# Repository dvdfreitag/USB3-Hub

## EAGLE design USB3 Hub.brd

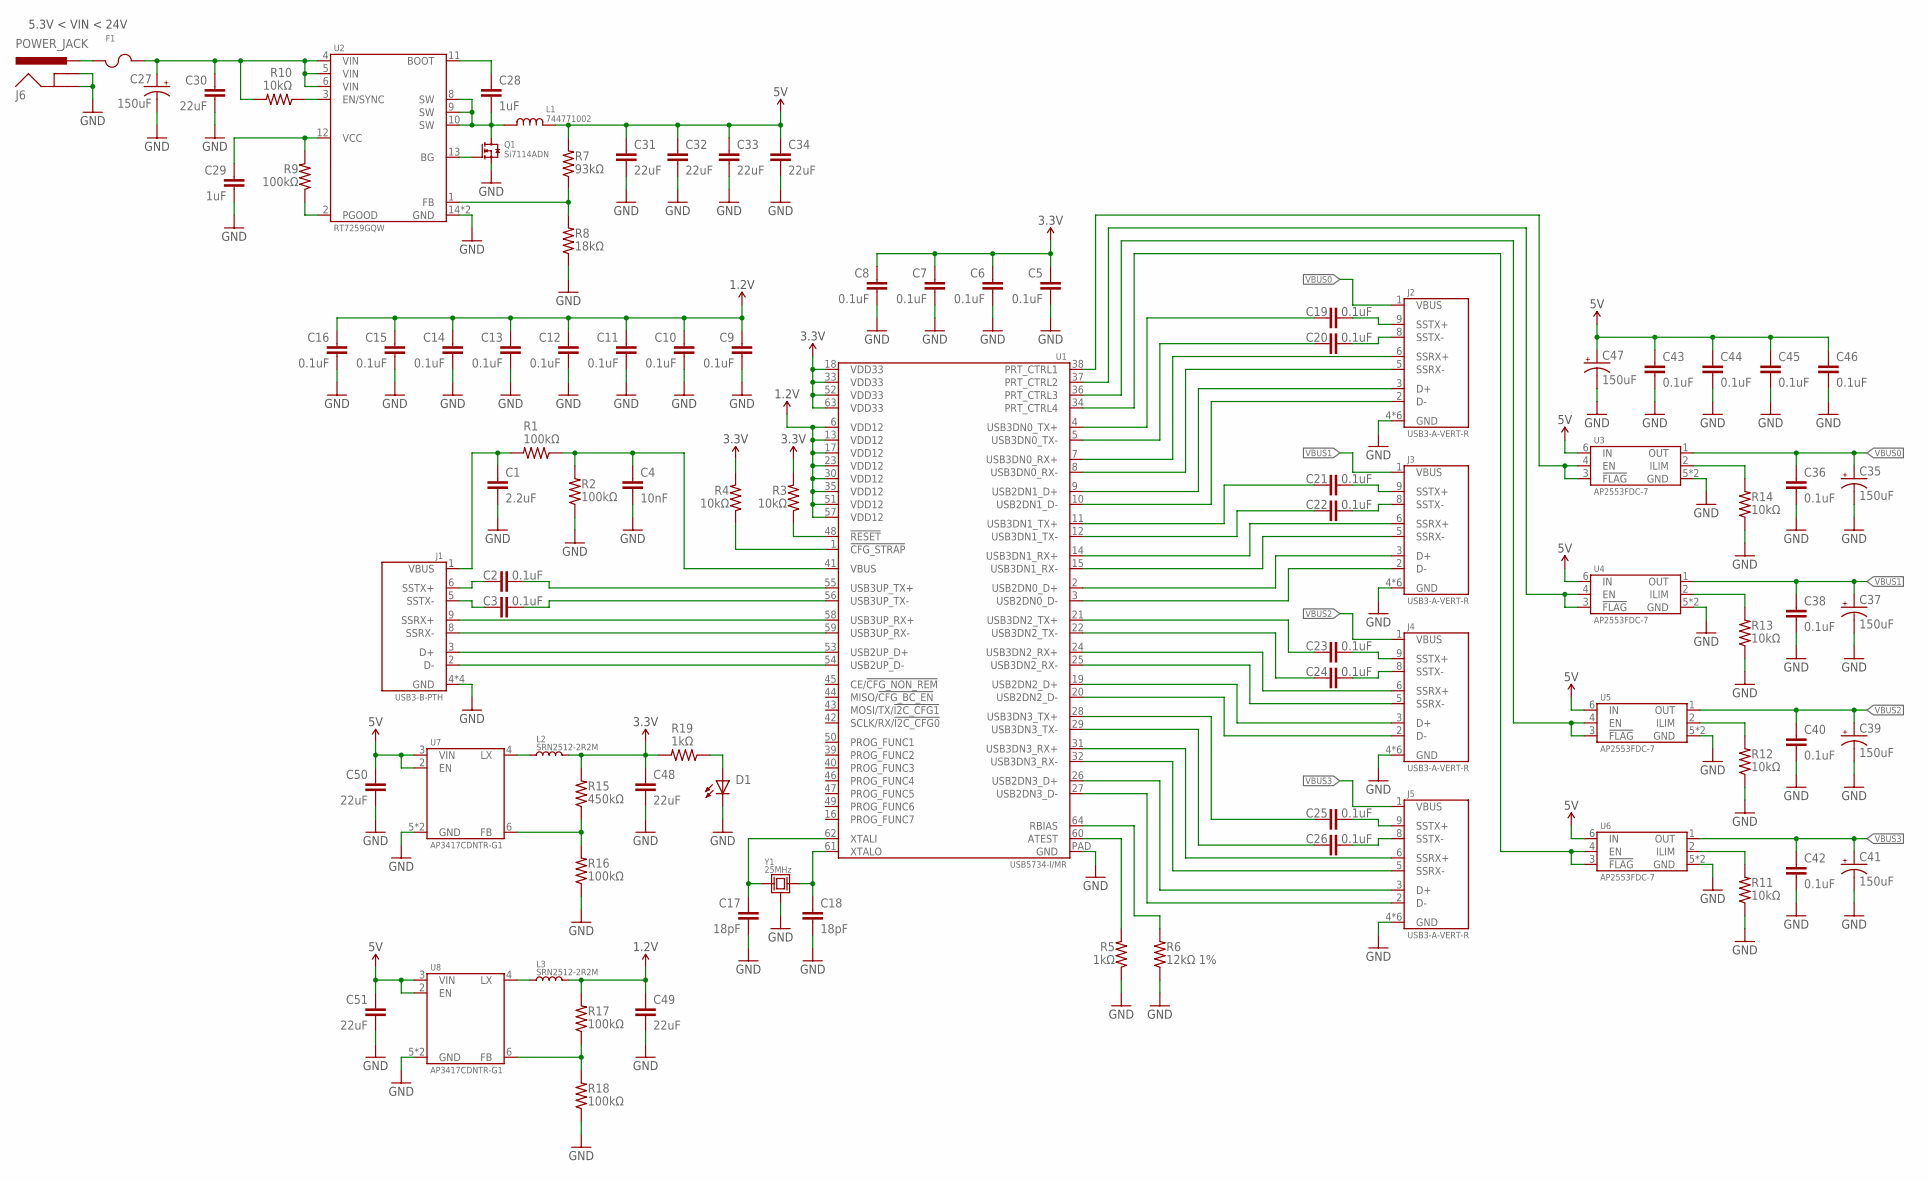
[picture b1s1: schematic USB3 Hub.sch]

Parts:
C1: 2.2uF; 0603-CAP
C2, C3, C5, C6, C7, C8, C9, C10, C11, C12, C13, C14, C15, C16, C19, C20, C21, C22, C23, C24, C25, C26, C36, C38, C40, C42, C43, C44, C45, C46: 0.1uF; 0603-CAP
C4: 10nF; 0603-CAP
C17, C18: 18pF; 0603-CAP
C27, C35, C37, C39, C41, C47: 150uF; CAP_POL-6.6X6.6
C28, C29: 1uF; 0603-CAP
C30, C31, C32, C33, C34, C48, C49, C50, C51: 22uF; 0603-CAP
D1: LED-0805; 0805-LED
F1: PTC-1812; 1812-PTC
J1: USB3-B-PTH; GSB4211311WEU
J2, J3, J4, J5: USB3-A-VERT-R; GSB4116341HR
J6: POWER_JACK; BARREL-POWER_2.1MMX5.5MM
L1: 744771002
L2, L3: SRN2512-2R2M; SRN2512
Q1: Si7114ADN; POWERPAK
R1, R2, R9, R16, R17, R18: 100kΩ; 0603-CAP
R3, R4, R10, R11, R12, R13, R14: 10kΩ; 0603-CAP
R5, R19: 1kΩ; 0603-CAP
R6: 12kΩ 1%; 0603-CAP
R7: 93kΩ; 0603-CAP
R8: 18kΩ; 0603-CAP
R15: 450kΩ; 0603-CAP
U1: USB5734-I/MR; VQFN-64-9MM
U2: RT7259GQW; WDFN-14-4X3
U3, U4, U5, U6: AP2553FDC-7; UDFN6-2020
U7, U8: AP3417CDNTR-G1; UDFN6-2020
Y1: 25MHz; FA-238

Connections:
1.2V: C9.1, C10.1, C11.1, C12.1, C13.1, C14.1, C15.1, C16.1, C49.1, L3.2, R17.2, U1.6 (VDD12), U1.13 (VDD12), U1.17 (VDD12), U1.23 (VDD12), U1.30 (VDD12), U1.35 (VDD12), U1.51 (VDD12), U1.57 (VDD12)
3.3V: C5.1, C6.1, C7.1, C8.1, C48.1, L2.2, R3.2, R4.2, R15.2, R19.2, U1.18 (VDD33), U1.33 (VDD33), U1.52 (VDD33), U1.63 (VDD33)
5V: C31.1, C32.1, C33.1, C34.1, C43.1, C44.1, C45.1, C46.1, C47.+, C50.1, C51.1, L1.P$2, R7.2, U3.6 (IN), U4.6 (IN), U5.6 (IN), U6.6 (IN), U7.2 (EN), U7.3 (VIN), U8.2 (EN), U8.3 (VIN)
D0_N: J2.2 (D-), U1.10 (USB2DN1_D-)
D0_P: J2.3 (D+), U1.9 (USB2DN1_D+)
D1_N: J3.2 (D-), U1.3 (USB2DN0_D-)
D1_P: J3.3 (D+), U1.2 (USB2DN0_D+)
D2_N: J4.2 (D-), U1.20 (USB2DN2_D-)
D2_P: J4.3 (D+), U1.19 (USB2DN2_D+)
D3_N: J5.2 (D-), U1.27 (USB2DN3_D-)
D3_P: J5.3 (D+), U1.26 (USB2DN3_D+)
D_N: J1.2 (D-), U1.54 (USB2UP_D-)
D_P: J1.3 (D+), U1.53 (USB2UP_D+)
GND: C1.2, C4.2, C5.2, C6.2, C7.2, C8.2, C9.2, C10.2, C11.2, C12.2, C13.2, C14.2, C15.2, C16.2, C17.2, C18.2, C27.-, C29.2, C30.2, C31.2, C32.2, C33.2, C34.2, C35.-, C36.2, C37.-, C38.2, C39.-, C40.2, C41.-, C42.2, C43.2, C44.2, C45.2, C46.2, C47.-, C48.2, C49.2, C50.2, C51.2, D1.C, J1.4 (GND), J1.7 (GND), J1.P$10 (GND), J1.P$11 (GND), J2.4 (GND), J2.7 (GND), J2.P$1 (GND), J2.P$2 (GND), J2.P$3 (GND), J2.P$4 (GND), J3.4 (GND), J3.7 (GND), J3.P$1 (GND), J3.P$2 (GND), J3.P$3 (GND), J3.P$4 (GND), J4.4 (GND), J4.7 (GND), J4.P$1 (GND), J4.P$2 (GND), J4.P$3 (GND), J4.P$4 (GND), J5.4 (GND), J5.7 (GND), J5.P$1 (GND), J5.P$2 (GND), J5.P$3 (GND), J5.P$4 (GND), J6.2 (GND), J6.3 (GNDBREAK), Q1.1 (SOURCE), Q1.2 (SOURCE), Q1.3 (SOURCE), R2.1, R5.1, R6.1, R8.1, R11.1, R12.1, R13.1, R14.1, R16.1, R18.1, U1.PAD (GND), U2.14 (GND), U2.PAD (GND), U3.5 (GND), U3.PAD (GND), U4.5 (GND), U4.PAD (GND), U5.5 (GND), U5.PAD (GND), U6.5 (GND), U6.PAD (GND), U7.5 (GND), U7.PAD (GND), U8.5 (GND), U8.PAD (GND), Y1.2 (GND), Y1.4 (GND)
unnamed: F1.1, J6.1 (PWR)
unnamed: C27.+, C30.1, F1.2, R10.2, U2.4 (VIN), U2.5 (VIN), U2.6 (VIN)
unnamed: R7.1, R8.2, U2.1 (FB)
unnamed: Q1.4 (GATE), U2.13 (BG)
unnamed: C1.1, J1.1 (VBUS), R1.2
unnamed: R12.2, U5.2 (ILIM)
unnamed: C28.2, L1.P$1, Q1.5 (DRAIN), Q1.6 (DRAIN), Q1.7 (DRAIN), Q1.8 (DRAIN), Q1.9 (DRAIN), Q1.10 (DRAIN), Q1.11 (DRAIN), U2.8 (SW), U2.9 (SW), U2.10 (SW)
unnamed: C28.1, U2.11 (BOOT)
unnamed: C29.1, R9.2, U2.12 (VCC)
unnamed: C4.1, R1.1, R2.2, U1.41 (VBUS)
unnamed: R9.1, U2.2 (PGOOD)
unnamed: R3.1, U1.48 (!RESET)
unnamed: R4.1, U1.1 (!CFG_STRAP)
unnamed: C17.1, U1.62 (XTALI), Y1.1
unnamed: C18.1, U1.61 (XTALO), Y1.3 (2)
unnamed: R5.2, U1.60 (ATEST)
unnamed: R6.2, U1.64 (RBIAS)
unnamed: R10.1, U2.3 (EN/SYNC)
unnamed: R11.2, U6.2 (ILIM)
unnamed: L3.1, U8.4 (LX)
unnamed: U1.36 (PRT_CTRL3), U5.3 (!FLAG), U5.4 (EN)
unnamed: U1.38 (PRT_CTRL1), U3.3 (!FLAG), U3.4 (EN)
unnamed: U1.37 (PRT_CTRL2), U4.3 (!FLAG), U4.4 (EN)
unnamed: R14.2, U3.2 (ILIM)
unnamed: R17.1, R18.2, U8.6 (FB)
unnamed: L2.1, U7.4 (LX)
unnamed: R13.2, U4.2 (ILIM)
unnamed: U1.34 (PRT_CTRL4), U6.3 (!FLAG), U6.4 (EN)
unnamed: R15.1, R16.2, U7.6 (FB)
unnamed: D1.A, R19.1
R0_N: J2.5 (SSRX-), U1.8 (USB3DN0_RX-)
R0_P: J2.6 (SSRX+), U1.7 (USB3DN0_RX+)
R1_N: J3.5 (SSRX-), U1.15 (USB3DN1_RX-)
R1_P: J3.6 (SSRX+), U1.14 (USB3DN1_RX+)
R2_N: J4.5 (SSRX-), U1.25 (USB3DN2_RX-)
R2_P: J4.6 (SSRX+), U1.24 (USB3DN2_RX+)
R3_N: J5.5 (SSRX-), U1.32 (USB3DN3_RX-)
R3_P: J5.6 (SSRX+), U1.31 (USB3DN3_RX+)
R_N: J1.8 (SSRX-), U1.59 (USB3UP_RX-)
R_P: J1.9 (SSRX+), U1.58 (USB3UP_RX+)
T0_N: C20.1, U1.5 (USB3DN0_TX-)
T0_P: C19.1, U1.4 (USB3DN0_TX+)
T1_N: C22.1, U1.12 (USB3DN1_TX-)
T1_P: C21.1, U1.11 (USB3DN1_TX+)
T2_N: C24.1, U1.22 (USB3DN2_TX-)
T2_P: C23.1, U1.21 (USB3DN2_TX+)
T3_N: C26.1, U1.29 (USB3DN3_TX-)
T3_P: C25.1, U1.28 (USB3DN3_TX+)
T_N: C3.2, U1.56 (USB3UP_TX-)
T_P: C2.2, U1.55 (USB3UP_TX+)
VBUS0: C35.+, C36.1, J2.1 (VBUS), U3.1 (OUT)
VBUS1: C37.+, C38.1, J3.1 (VBUS), U4.1 (OUT)
VBUS2: C39.+, C40.1, J4.1 (VBUS), U5.1 (OUT)
VBUS3: C41.+, C42.1, J5.1 (VBUS), U6.1 (OUT)
_T0_N: C20.2, J2.8 (SSTX-)
_T0_P: C19.2, J2.9 (SSTX+)
_T1_N: C22.2, J3.8 (SSTX-)
_T1_P: C21.2, J3.9 (SSTX+)
_T2_N: C24.2, J4.8 (SSTX-)
_T2_P: C23.2, J4.9 (SSTX+)
_T3_N: C26.2, J5.8 (SSTX-)
_T3_P: C25.2, J5.9 (SSTX+)
_T_N: C3.1, J1.5 (SSTX-)
_T_P: C2.1, J1.6 (SSTX+)

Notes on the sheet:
5.3V < VIN < 24V

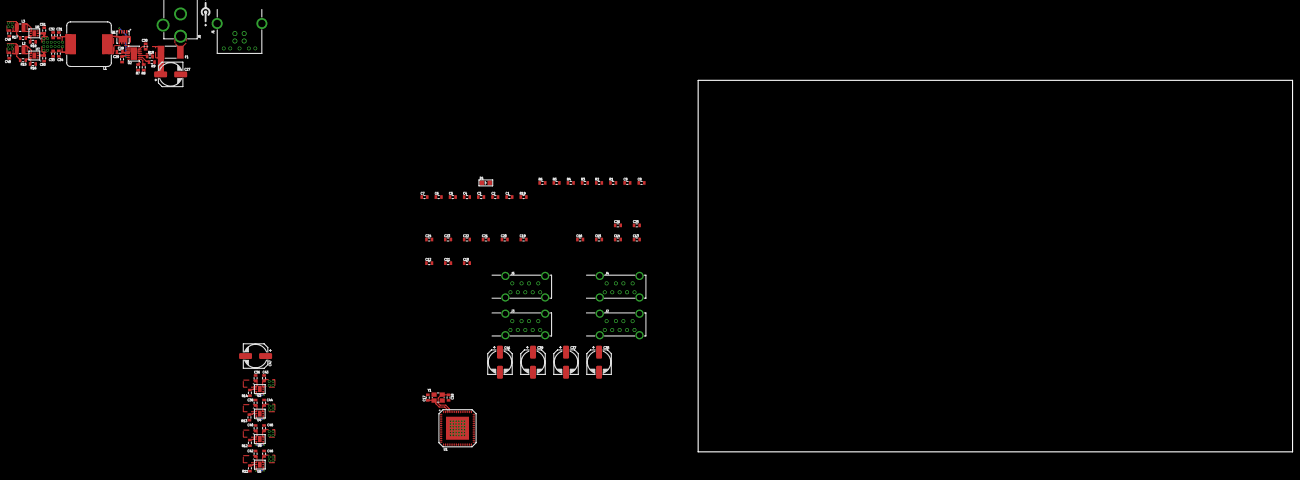
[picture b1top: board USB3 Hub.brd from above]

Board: 4 copper layers, 160.0 x 100.0 mm, 91 parts (0 on the bottom side), 78 nets.

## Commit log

2016-08-18 Update board files
    Changes to the main switching mosfet and start the board layout
